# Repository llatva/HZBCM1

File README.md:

# HZBCM1
ATMEGA16/32 CPU board by Lasse OH3HZB 2012

Multi-purpose CPU board (dimensions 5cm x 5cm) for IoT applications.
Designed in Cadsoft Eagle some years ago (when they didn't call it
IoT yet :) Design files (.sch and .brd) should open at least with Eagle 7.60.

Released under the MIT license (see attached).

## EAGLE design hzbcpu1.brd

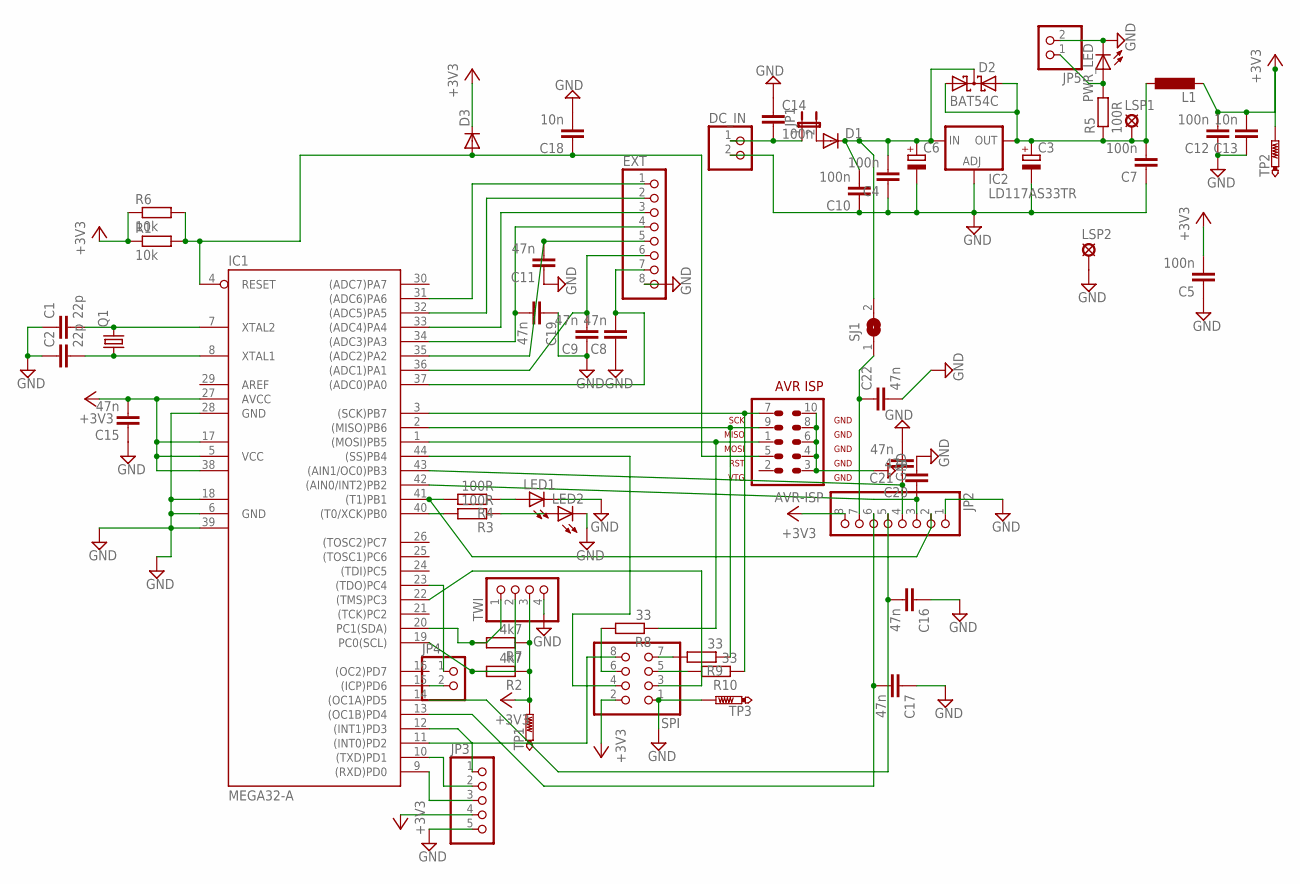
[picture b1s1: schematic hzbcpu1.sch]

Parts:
AVR-ISP: AVR-ISP-10
C1, C2: 22p; C1206
C3, C6: CPOL-EUSMCD; SMC_D
C4, C7, C10, C12, C14: 100n; C1206
C5: 100n; C0805
C8, C9, C11, C15, C19, C20, C21, C22: 47n; C1206
C13, C18: 10n; C0805
C16, C17: 47n; C0805
D1, D3: DIODE-DO214AA; DO214AA
D2: BAT54C; SOT23
DC_IN: PINHD-1X2; 1X02
EXT: PINHD-1X8; 1X08
IC1: MEGA32-A; TQFP44
IC2: LD117AS33TR; SOT223
JP1: JP1E; JP1
JP2: PINHD-1X8; 1X08
JP3: PINHD-1X5; 1X05
JP4, JP5: PINHD-1X2; 1X02
L1: L-EUL3225M; L3225M
LED1, LED2: LED3MM
LSP1, LSP2: LSP11
PWR_LED: LED3MM
Q1: CRYSTALHC49UP; HC49UP
R1: 10k; 0204/7
R2, R7: 4k7; R1206
R3, R4, R5: 100R; R1206
R6: 10k; R1206
R8, R9: 33; R0805
R10: 33; R1206
SJ1: SJ
SPI: PINHD-2X4; 2X04
TP1, TP2, TP3: PTR1B1,27; B1,27
TWI: PINHD-1X4; 1X04

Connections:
+3V3: C5.2, C12.2, C13.2, C15.2, D3.C, IC1.5 (VCC), IC1.17 (VCC1), IC1.27 (AVCC), IC1.38 (VCC2), JP2.8, JP3.4, L1.2, R1.1, R2.1, R6.1, R7.1, SPI.2, TP1.TP, TP2.TP, TWI.3
GND: AVR-ISP.3, AVR-ISP.4, AVR-ISP.6, AVR-ISP.8, AVR-ISP.10, C1.1, C2.1, C3.-, C4.1, C5.1, C6.-, C7.1, C8.1, C9.1, C10.1, C11.1, C12.1, C13.1, C14.1, C15.1, C16.1, C17.1, C18.2, C19.1, C20.2, C21.2, C22.2, DC_IN.2, EXT.8, IC1.6 (GND), IC1.18 (GND1), IC1.28 (GND), IC1.39 (GND2), IC2.1 (ADJ), JP2.1, JP3.5, JP5.2, LED1.K (C), LED2.K (C), LSP2.MP, PWR_LED.K (C), SPI.1, TP3.TP, TWI.4
unnamed: AVR-ISP.5, C18.1, D3.A, IC1.4 (RESET), R1.2, R6.2
unnamed: R8.2, SPI.6
unnamed: C2.2, IC1.8 (XTAL1), Q1.1
unnamed: C1.2, IC1.7 (XTAL2), Q1.2
unnamed: R9.2, SPI.7
unnamed: AVR-ISP.7, IC1.3 ((SCK)PB7), R10.1
unnamed: EXT.1, IC1.31 ((ADC6)PA6)
unnamed: IC1.20 (PC1(SDA)), R7.2, TWI.1
unnamed: IC1.40 ((T0/XCK)PB0), R3.2
unnamed: C4.2, C6.+, C10.2, D1.C, D2.3 (CC), IC2.3 (IN), SJ1.2
unnamed: IC1.19 (PC0(SCL)), R2.2, TWI.2
unnamed: IC1.11 ((INT0)PD2), SPI.8
unnamed: C14.2, DC_IN.1, JP1.1
unnamed: C20.1, IC1.42 ((AIN0/INT2)PB2), JP2.3
unnamed: IC1.9 ((RXD)PD0), JP3.3
unnamed: C19.2, EXT.4, IC1.34 ((ADC3)PA3)
unnamed: EXT.3, IC1.33 ((ADC4)PA4)
unnamed: EXT.2, IC1.32 ((ADC5)PA5)
unnamed: C21.1, IC1.43 ((AIN1/OC0)PB3), JP2.4
unnamed: C8.2, EXT.7, IC1.37 ((ADC0)PA0)
unnamed: D1.A, JP1.2
unnamed: C9.2, EXT.6, IC1.36 ((ADC1)PA1)
unnamed: IC1.41 ((T1)PB1), JP2.2, R4.2
unnamed: C11.2, EXT.5, IC1.35 ((ADC2)PA2)
unnamed: IC1.10 ((TXD)PD1), JP3.2
unnamed: IC1.44 ((SS)PB4), SPI.4
unnamed: JP5.1, PWR_LED.A, R5.2
unnamed: LED2.A, R3.1
unnamed: AVR-ISP.1, IC1.1 ((MOSI)PB5), R8.1
unnamed: AVR-ISP.9, IC1.2 ((MISO)PB6), R9.1
unnamed: R10.2, SPI.5
unnamed: C17.2, IC1.13 ((OC1B)PD4), JP2.6
unnamed: C16.2, IC1.14 ((OC1A)PD5), JP2.5
unnamed: C3.+, C7.2, D2.1 (A1), D2.2 (A2), IC2.4 (OUT), L1.1, LSP1.MP, R5.1
unnamed: LED1.A, R4.1
unnamed: IC1.15 ((ICP)PD6), JP4.2
unnamed: IC1.22 ((TMS)PC3), SPI.3
unnamed: C22.1, JP2.7, SJ1.1
unnamed: IC1.23 ((TDO)PC4), JP4.1
unnamed: IC1.12 ((INT1)PD3), JP3.1

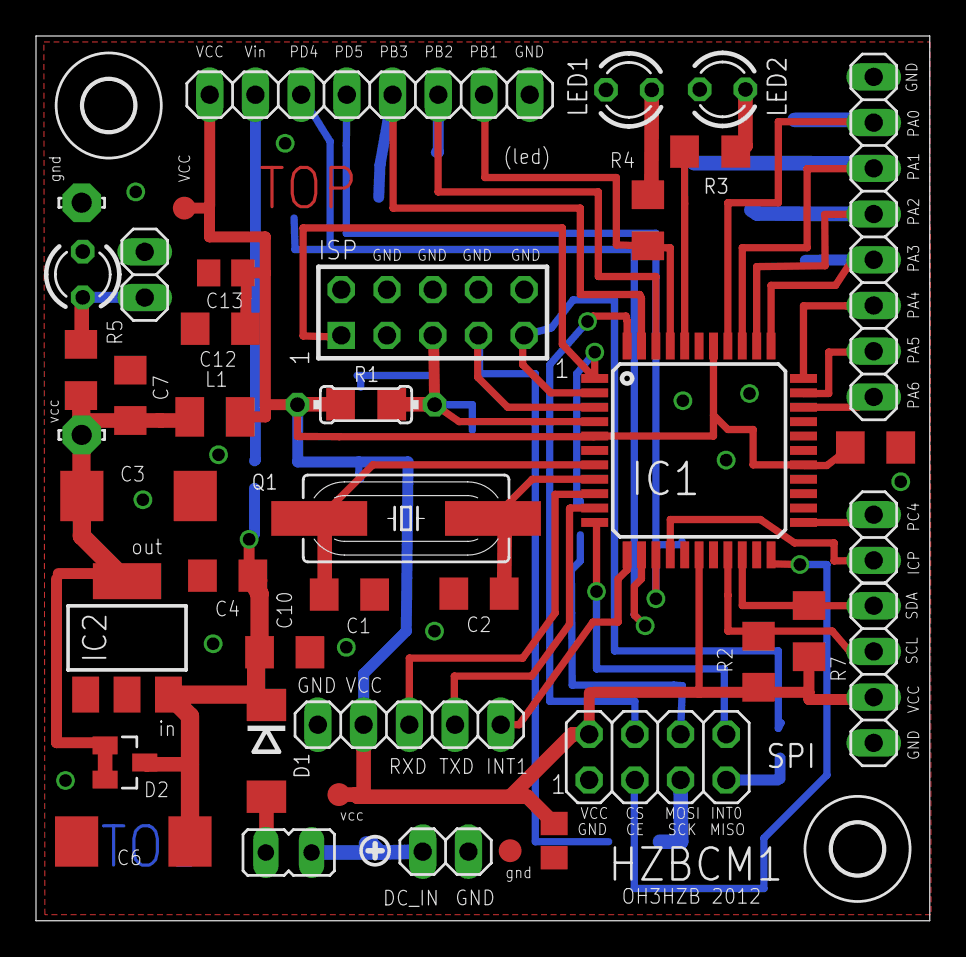
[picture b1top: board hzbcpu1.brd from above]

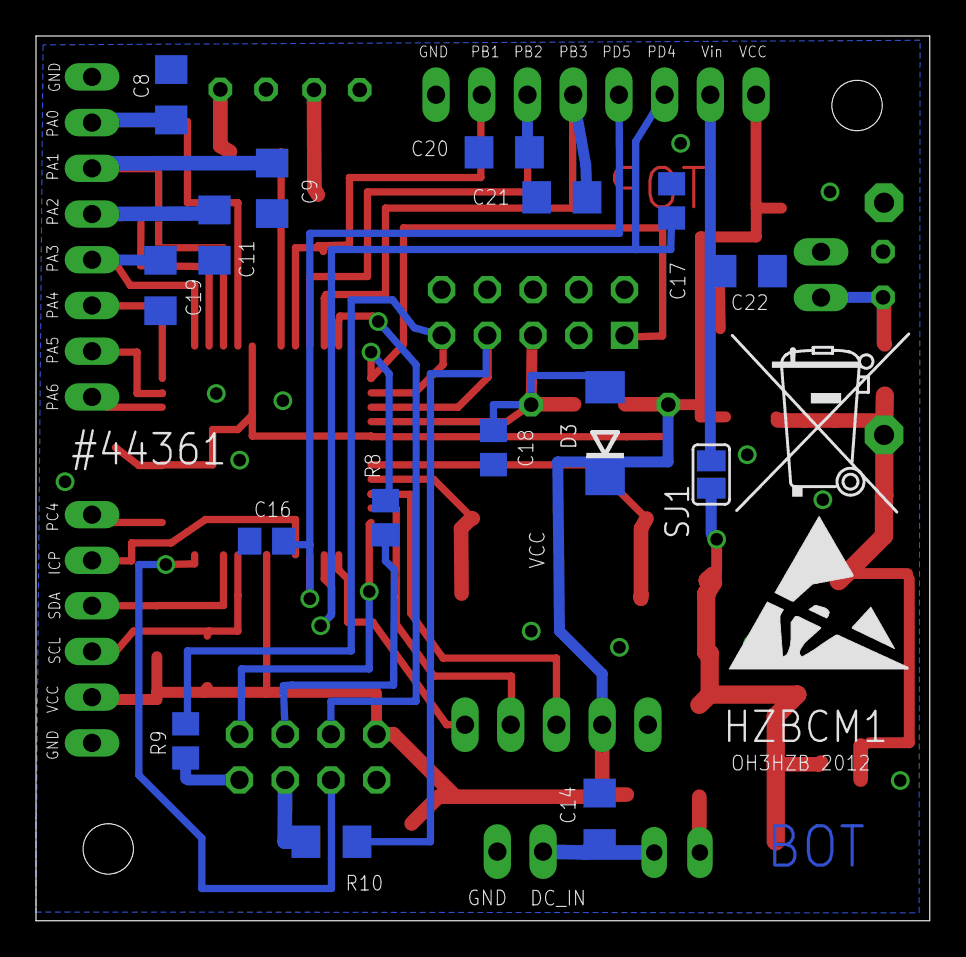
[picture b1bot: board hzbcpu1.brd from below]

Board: 2 copper layers, 49.7 x 49.2 mm, 63 parts (18 on the bottom side), 42 nets.

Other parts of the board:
U$1, U$2: 2,8
U$3: ESD_10.00
U$4: MUELLTONNE_10.00
U$5: ICON_PLUS

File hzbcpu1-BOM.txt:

Partlist

Exported from hzbcpu1.sch at 7.1.2022 12.55

EAGLE Version 7.6.0 Copyright (c) 1988-2016 CadSoft

Assembly variant: 

Part     Value          Device        Package    Library  Sheet

AVR-ISP  AVR-ISP-10     AVR-ISP-10    AVR-ISP-10 avr-6    1
C1       22p            C-EUC1206     C1206      rcl      1
C2       22p            C-EUC1206     C1206      rcl      1
C3                      CPOL-EUSMCD   SMC_D      rcl      1
C4       100n           C-EUC1206     C1206      rcl      1
C5       100n           C-EUC0805     C0805      rcl      1
C6                      CPOL-EUSMCD   SMC_D      rcl      1
C7       100n           C-EUC1206     C1206      rcl      1
C8       47n            C-EUC1206     C1206      rcl      1
C9       47n            C-EUC1206     C1206      rcl      1
C10      100n           C-EUC1206     C1206      rcl      1
C11      47n            C-EUC1206     C1206      rcl      1
C12      100n           C-EUC1206     C1206      rcl      1
C13      10n            C-EUC0805     C0805      rcl      1
C14      100n           C-EUC1206     C1206      rcl      1
C15      47n            C-EUC1206     C1206      rcl      1
C16      47n            C-EUC0805     C0805      rcl      1
C17      47n            C-EUC0805     C0805      rcl      1
C18      10n            C-EUC0805     C0805      rcl      1
C19      47n            C-EUC1206     C1206      rcl      1
C20      47n            C-EUC1206     C1206      rcl      1
C21      47n            C-EUC1206     C1206      rcl      1
C22      47n            C-EUC1206     C1206      rcl      1
D1                      DIODE-DO214AA DO214AA    diode    1
D2       BAT54C         BAT54C        SOT23      diode    1
D3                      DIODE-DO214AA DO214AA    diode    1
DC_IN                   PINHD-1X2     1X02       pinhead  1
EXT                     PINHD-1X8     1X08       pinhead  1
IC1      MEGA32-A       MEGA32-A      TQFP44     atmel    1
IC2      LD117AS33TR    LD117AS33TR   SOT223     v-reg    1
JP1                     JP1E          JP1        jumper   1
JP2                     PINHD-1X8     1X08       pinhead  1
JP3                     PINHD-1X5     1X05       pinhead  1
JP4                     PINHD-1X2     1X02       pinhead  1
JP5                     PINHD-1X2     1X02       pinhead  1
L1                      L-EUL3225M    L3225M     rcl      1
LED1                    LED3MM        LED3MM     led      1
LED2                    LED3MM        LED3MM     led      1
LSP1     LSP11          LSP11         LSP11      solpad   1
LSP2     LSP11          LSP11         LSP11      solpad   1
PWR_LED                 LED3MM        LED3MM     led      1
Q1                      CRYSTALHC49UP HC49UP     crystal  1
R1       10k            R-EU_0204/7   0204/7     rcl      1
R2       4k7            R-EU_R1206    R1206      rcl      1
R3       100R           R-EU_R1206    R1206      rcl      1
R4       100R           R-EU_R1206    R1206      rcl      1
R5       100R           R-EU_R1206    R1206      rcl      1
R6       10k            R-EU_R1206    R1206      rcl      1
R7       4k7            R-EU_R1206    R1206      rcl      1
R8       33             R-EU_R0805    R0805      rcl      1
R9       33             R-EU_R0805    R0805      rcl      1
R10      33             R-EU_R1206    R1206      rcl      1
SJ1                     SJ            SJ         jumper   1
SPI                     PINHD-2X4     2X04       pinhead  1
TP1      PTR1B1,27      PTR1B1,27     B1,27      testpad  1
TP2      PTR1B1,27      PTR1B1,27     B1,27      testpad  1
TP3      PTR1B1,27      PTR1B1,27     B1,27      testpad  1
TWI                     PINHD-1X4     1X04       pinhead  1

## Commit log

2022-01-07 Published to Github
2022-01-07 Gerbers need to be re-generated as they may contain order number.
